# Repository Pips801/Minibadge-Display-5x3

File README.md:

# Minibadge-Display-5x3
 Battery-powered 5x3 SAINTCON Minibadge display

## Description
Battery-powered RP2040 controlled 5x3 minibadge display

MCU: RP2040

Battery: 606090 5000mAh + JST XH 3 pin 2.54mm

BMS: BQ25895

LEDs: WS2812B-2020

## Costs

| Completed?    | Purchase type    | Price   | Cost per item       |
| ------------- | ---------------- | ------- | ------------------- |
| No            | Parts            | $161.01 | $3.22               |
| No            | Main PCB         | $69.00  | $1.38               |
| No            | PCBA             | $101.84 | $2.04               |
| No            | Batteries        | $215.00 | $4.30               |
| No            | Front PCB        | $50.01  | $1.00               |
| No            | PCB Shipping     | $150.00 | $3.00               |
| No            | Battery Shipping | $100.00 | $2.00               |
| **Item quantity** |                  | **Total**   | **Total cost per item** |
| 50            |                  | $846.86 | $16.94              |

| Completed?    | Purchase type    | Price   | Cost per item       |
| ------------- | ---------------- | ------- | ------------------- |
| No            | Parts            | $131.22 | $5.25               |
| No            | Main PCB         | $28.70  | $1.15               |
| No            | PCBA             | $57.11  | $2.28               |
| No            | Batteries        | $107.50 | $4.30               |
| No            | Front PCB        | $37.50  | $1.50               |
| No            | PCB Shipping     | $80.00  | $3.20               |
| No            | Battery Shipping | $53.35  | $2.13               |
| **Item quantity** |                  | **Total**   | **Total cost per item** |
| 25            |                  | $495.38 | $19.82              |

## BOM

|Designator                                                                                        |Footprint                                                 |Quantity|Value            |LCSC Part #|
|--------------------------------------------------------------------------------------------------|----------------------------------------------------------|--------|-----------------|-----------|
|C1, C12, C13, C14, C15, C16, C17, C18, C19                                                        |0603                                                      |9       |4.7μF            |           |
|C10, C11, C20, C21, C22, C23, C24, C25, C26, C27, C28, C29, C34, C35, C36, C37, C38, C39, C40, C41|0402                                                      |20      |0.1μF            |           |
|C2, C3, C6, C7, C9                                                                                |0603                                                      |5       |10μF             |           |
|C31                                                                                               |0402                                                      |1       |1µF              |           |
|C32, C33                                                                                          |0402                                                      |2       |15pF             |           |
|C4                                                                                                |1206                                                      |1       |40μF             |C426659    |
|C5                                                                                                |0402                                                      |1       |47nF             |           |
|C8                                                                                                |0402                                                      |1       |1µF              |C52923     |
|D1                                                                                                |D_SMB                                                     |1       |20v 5A           |C14651     |
|D2, D3, D4, D5, D6, D7, D8, D9                                                                    |LED_WS2812B-2020_PLCC4_2.0x2.0mm                          |8       |WS2812B-2020     |C5349955   |
|J1                                                                                                |PinSocket_2x05_P2.54mm_Vertical_SMD                       |1       |Board to Board   |           |
|J2                                                                                                |JST_XH_S3B-XH-SM4-TB_1x03-1MP_P2.50mm_Horizontal          |1       |BATT JST         |C161860    |
|L1                                                                                                |L_Vishay_IHLP-2525                                        |1       |2.2µH            |C540967    |
|P1                                                                                                |USB_C_Receptacle_HRO_TYPE-C-31-M-12                       |1       |USB_C_Plug_USB2.0|C165948    |
|R1                                                                                                |0603                                                      |1       |5.23kΩ           |           |
|R10, R9                                                                                           |0402                                                      |2       |27.4Ω            |           |
|R11, R12, R13, R14, R15, R16                                                                      |0603                                                      |6       |10kΩ             |           |
|R2                                                                                                |0603                                                      |1       |260Ω             |C861779    |
|R3                                                                                                |0603                                                      |1       |30.1kΩ           |           |
|R4, R5                                                                                            |0603                                                      |2       |5.1k             |           |
|R6, R7, R8                                                                                        |0603                                                      |3       |1kΩ              |           |
|SW1                                                                                               |SW_Push_1P1T_XKB_TS-1187A                                 |1       |USB BOOT         |C318884    |
|U1                                                                                                |Texas_RTW_WQFN-24-1EP_4x4mm_P0.5mm_EP2.7x2.7mm_ThermalVias|1       |BQ25895          |C80200     |
|U10                                                                                               |Crystal_SMD_Abracon_ABM8G-4Pin_3.2x2.5mm                  |1       |ABM8-272-T3      |C20625731  |
|U2                                                                                                |SOIC-8_5.23x5.23mm_P1.27mm                                |1       |W25Q32JVSS       |C82344     |
|U3                                                                                                |QFN-10-RSE                                                |1       |TS3USB221A       |C128396    |
|U4, U5, U6, U7                                                                                    |SOT-223-3_TabPin2                                         |4       |AP7361C-33E      |C500795    |
|U8                                                                                                |SOIC-8_3.9x4.9mm_P1.27mm                                  |1       |TPM8837C         |C7436831   |
|U9                                                                                                |QFN-56-1EP_7x7mm_P0.4mm_EP3.2x3.2mm_ThermalVias           |1       |RP2040           |C2040      |

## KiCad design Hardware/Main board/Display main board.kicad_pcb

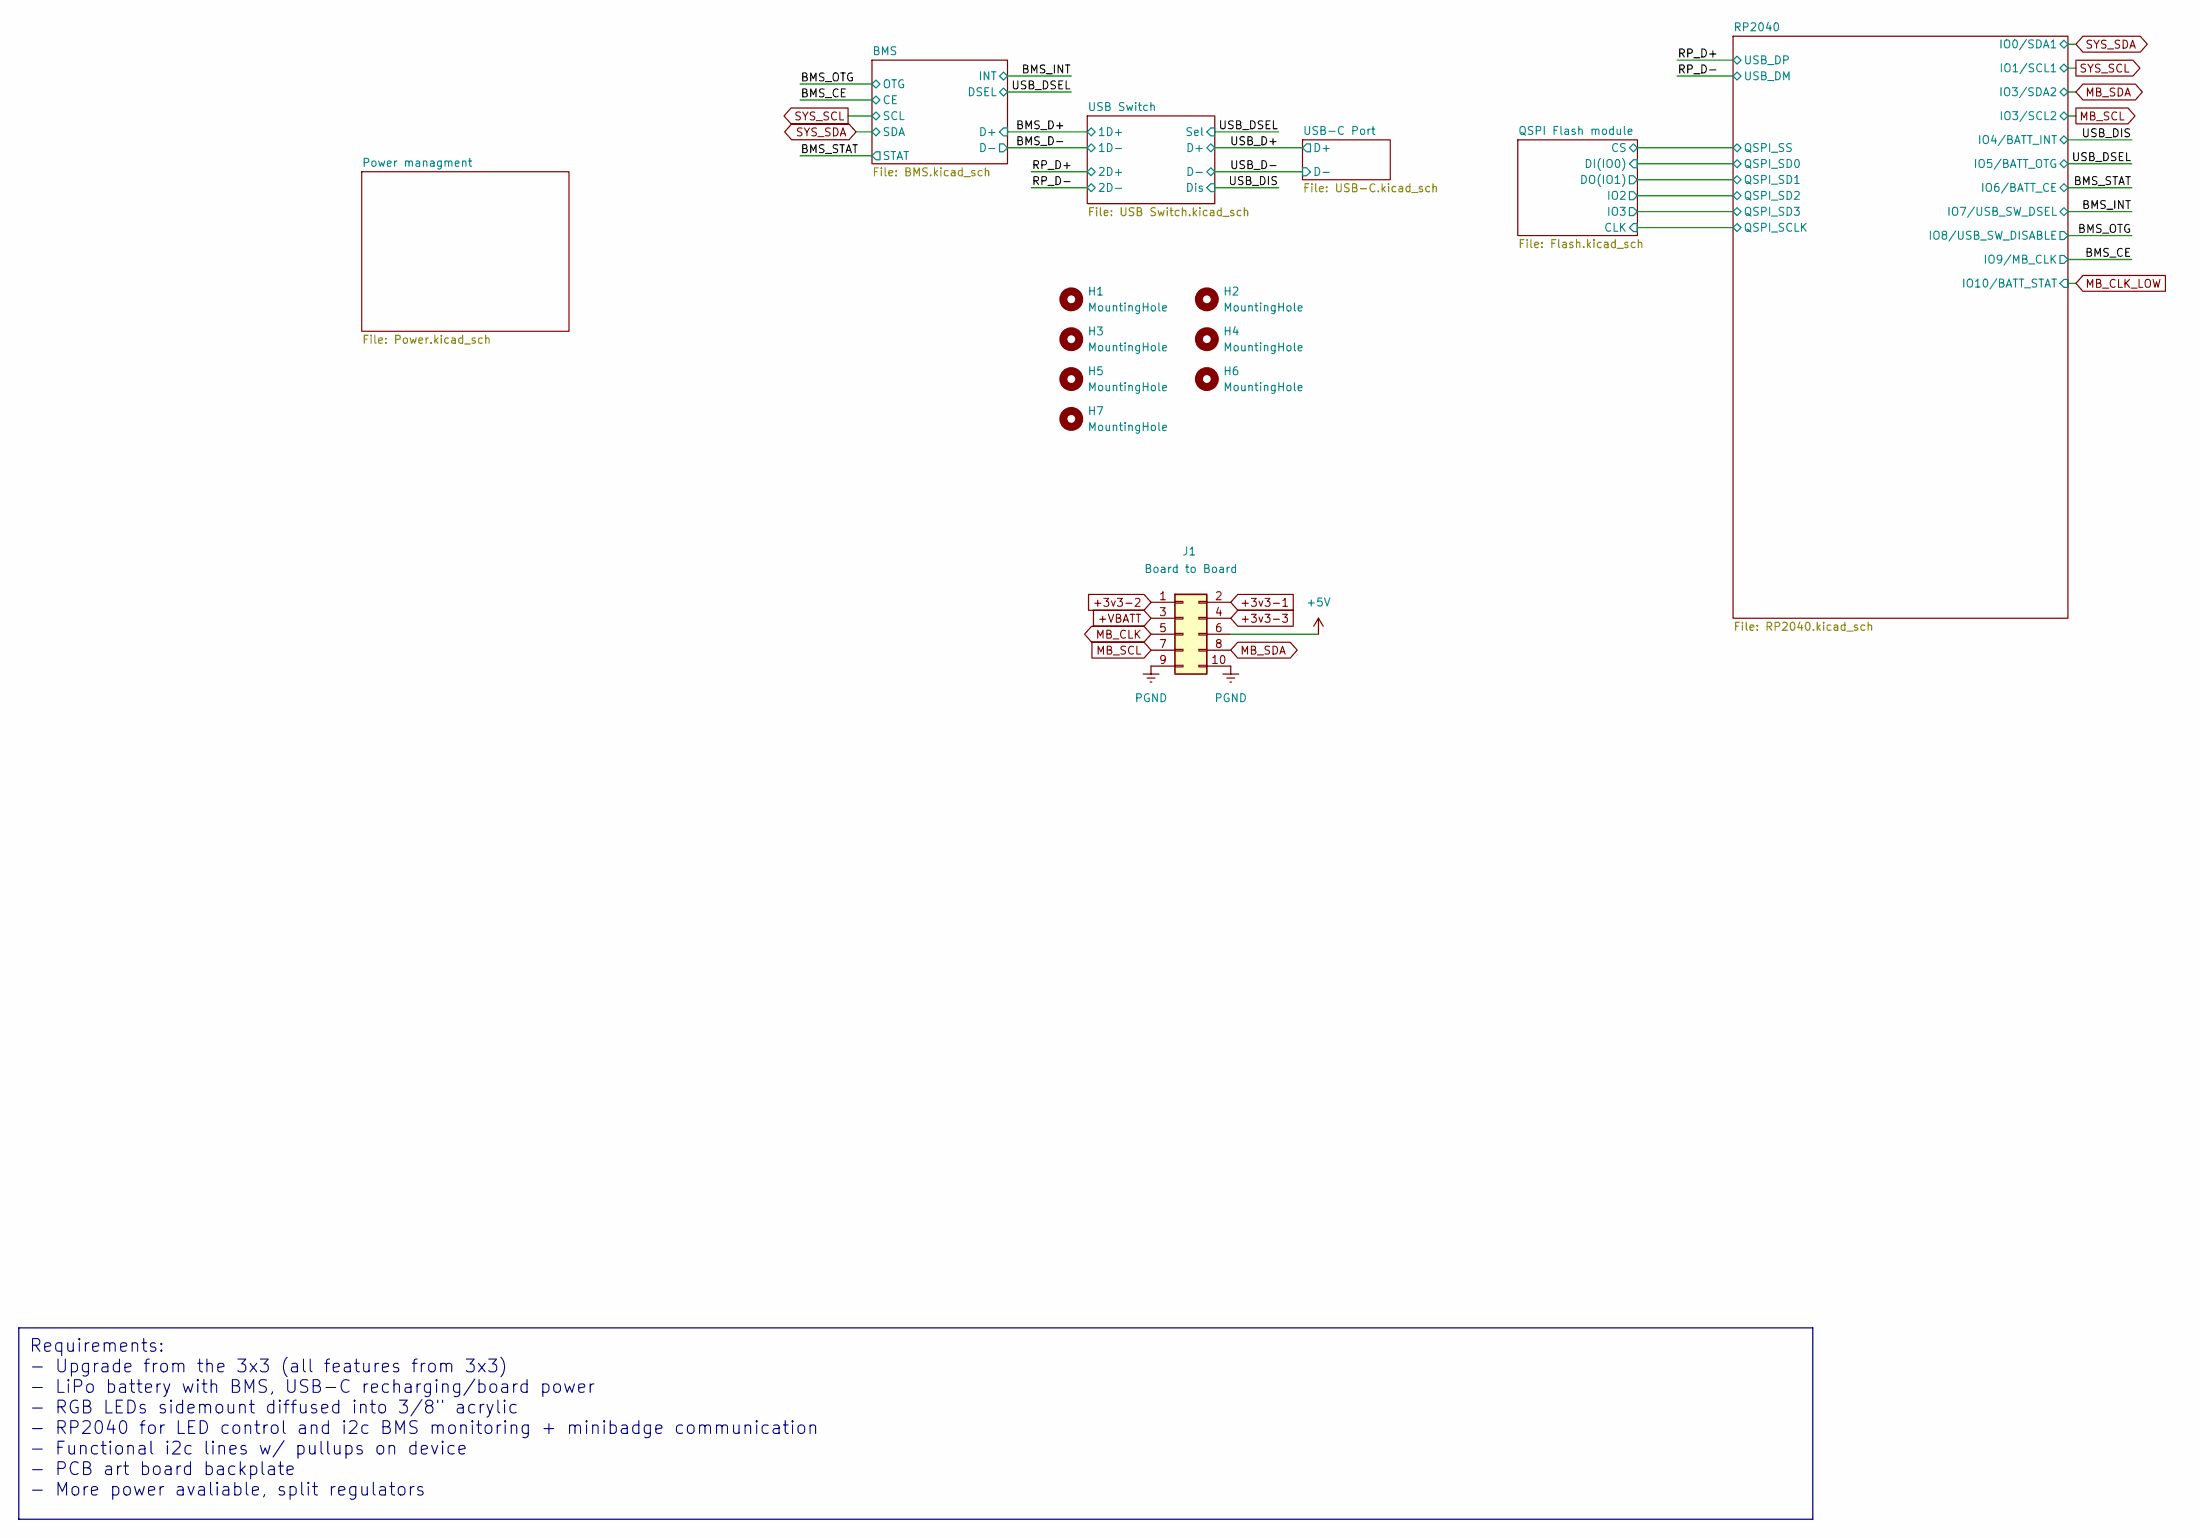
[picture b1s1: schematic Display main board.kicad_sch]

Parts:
H1, H2, H3, H4, H5, H6, H7: MountingHole; MountingHole_2.2mm_M2
J1: Board to Board; PinSocket_2x05_P2.54mm_Vertical_SMD

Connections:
+3v3-1: J1.2; also elsewhere on the board
+3v3-2: J1.1; also elsewhere on the board
+3v3-3: J1.4; also elsewhere on the board
+5V: J1.6; also elsewhere on the board
+VBATT: J1.3; also elsewhere on the board
MB_CLK: J1.5; also elsewhere on the board
MB_SCL: J1.7; also elsewhere on the board
MB_SDA: J1.8; also elsewhere on the board
PGND: J1.9, J1.10; also elsewhere on the board

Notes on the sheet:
Requirements: - Upgrade from the 3x3 (all features from 3x3) - LiPo battery with BMS, USB-C recharging/board power - RGB LEDs sidemount diffused into 3/8" acrylic - RP2040 for LED control and i2c BMS monitoring + minibadge communication - Functional i2c lines w/ pullups on device - PCB art board ba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

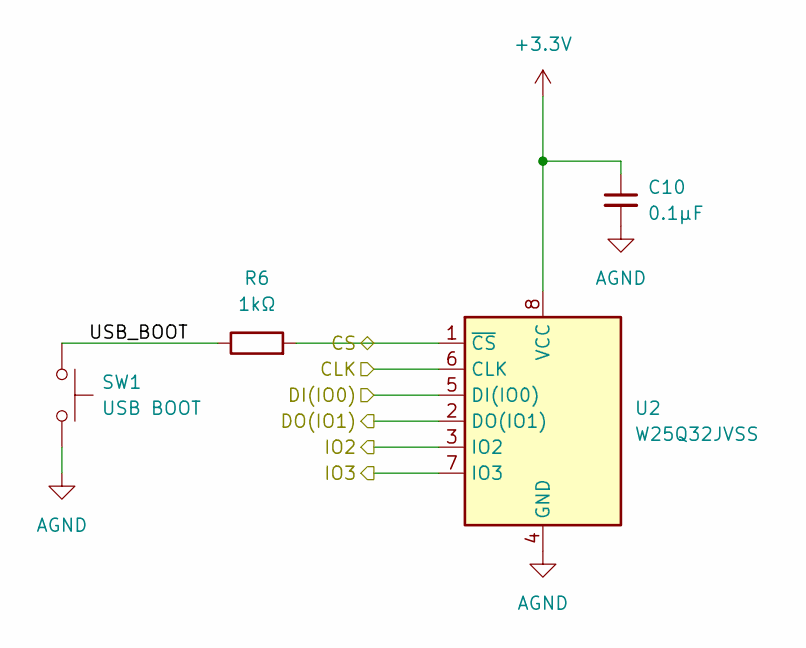
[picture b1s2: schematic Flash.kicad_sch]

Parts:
C10: 0.1μF; C_0402_1005Metric
R6: 1kΩ; R_0603_1608Metric
SW1: USB BOOT; SW_Push_1P1T_XKB_TS-1187A; LCSC Part # C318884
U2: W25Q32JVSS; SOIC-8_5.23x5.23mm_P1.27mm; JLCPCB Part # C82344

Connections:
+3.3V: C10.1, U2.8 (VCC); also elsewhere on the board
/QSPI Flash module/CLK: U2.6 (CLK); also elsewhere on the board
/QSPI Flash module/CS: R6.2, U2.1 (~CS); also elsewhere on the board
/QSPI Flash module/DI(IO0): U2.5 (DI(IO0)); also elsewhere on the board
/QSPI Flash module/DO(IO1): U2.2 (DO(IO1)); also elsewhere on the board
/QSPI Flash module/IO2: U2.3 (IO2); also elsewhere on the board
/QSPI Flash module/IO3: U2.7 (IO3); also elsewhere on the board
/QSPI Flash module/USB_BOOT: R6.1, SW1.1
AGND: C10.2, SW1.2, U2.4 (GND); also elsewhere on the board

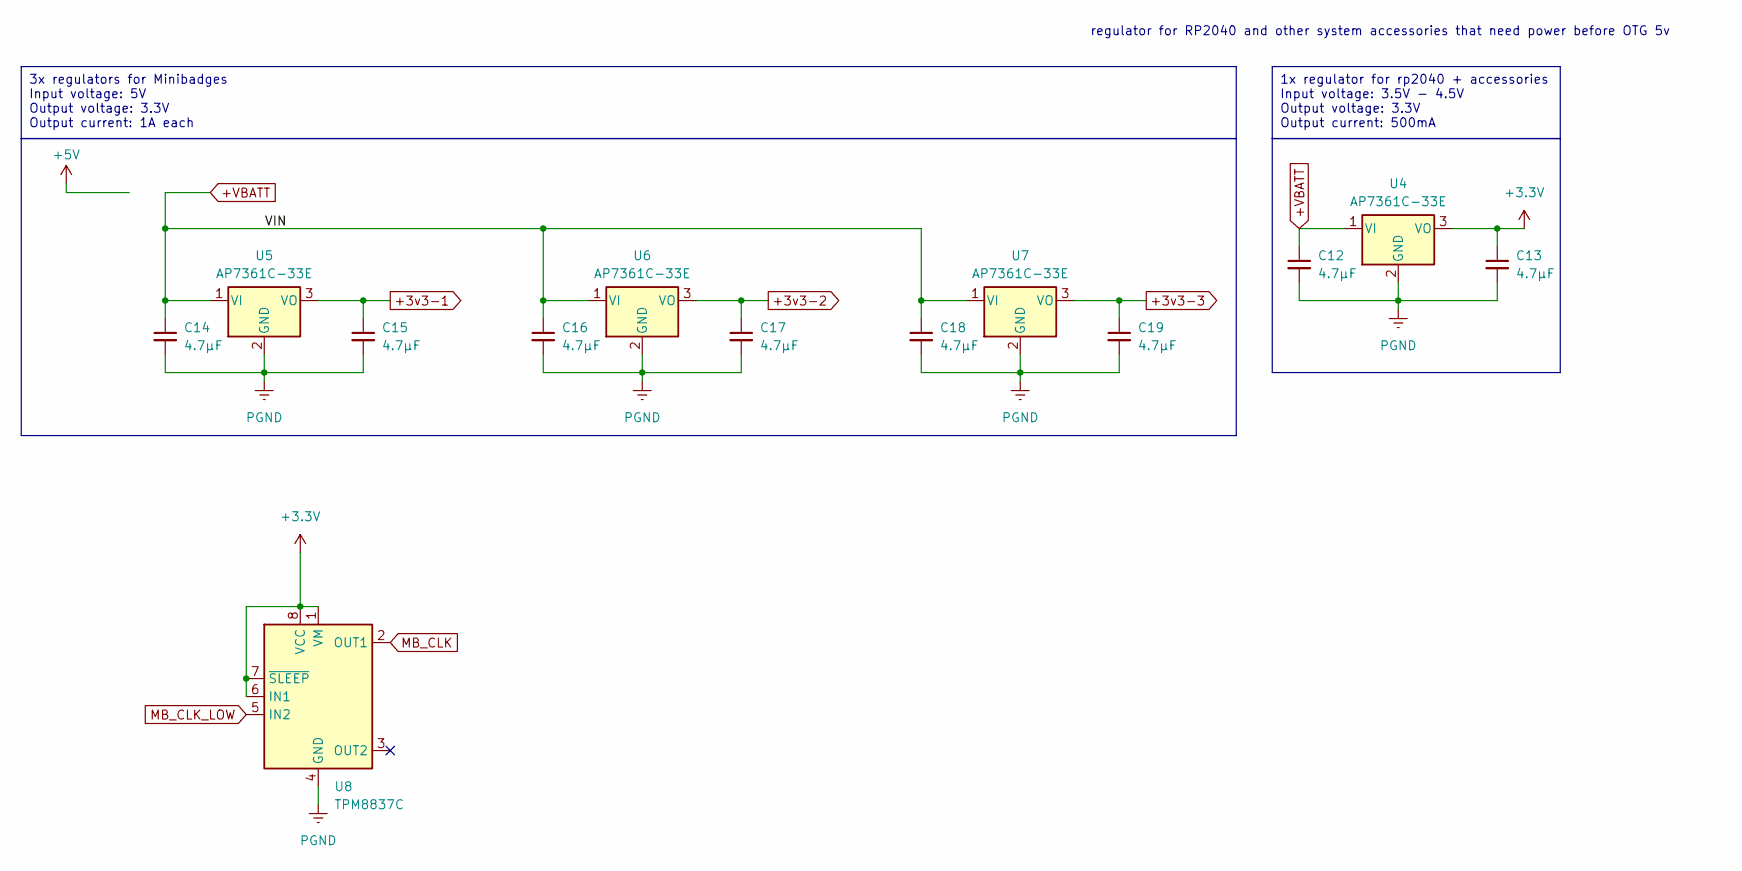
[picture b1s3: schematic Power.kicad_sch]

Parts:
C12, C13, C14, C15, C16, C17, C18, C19: 4.7μF; C_0603_1608Metric
U4, U5, U6, U7: AP7361C-33E; SOT-223-3_TabPin2; JLCPCB Part # C500795
U8: TPM8837C; SOIC-8_3.9x4.9mm_P1.27mm; JLCPCB Part # C7436831

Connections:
+3.3V: C13.1, U4.3 (VO), U8.1 (VM), U8.6 (IN1), U8.7 (~SLEEP), U8.8 (VCC); also elsewhere on the board
+3v3-1: C15.1, U5.3 (VO); also elsewhere on the board
+3v3-2: C17.1, U6.3 (VO); also elsewhere on the board
+3v3-3: C19.1, U7.3 (VO); also elsewhere on the board
+VBATT: C12.1, C14.1, C16.1, C18.1, U4.1 (VI), U5.1 (VI), U6.1 (VI), U7.1 (VI); also elsewhere on the board
MB_CLK: U8.2 (OUT1); also elsewhere on the board
MB_CLK_LOW: U8.5 (IN2); also elsewhere on the board
PGND: C12.2, C13.2, C14.2, C15.2, C16.2, C17.2, C18.2, C19.2, U4.2 (GND), U5.2 (GND), U6.2 (GND), U7.2 (GND), U8.4 (GND), U8.9 (GND); also elsewhere on the board

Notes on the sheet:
1x regulator for rp2040 + accessories Input voltage: 3.5V - 4.5V Output voltage: 3.3V Output current: 500mA
3x regulators for Minibadges Input voltage: 5V Output voltage: 3.3V Output current: 1A each
regulator for RP2040 and other system accessories that need power before OTG 5v

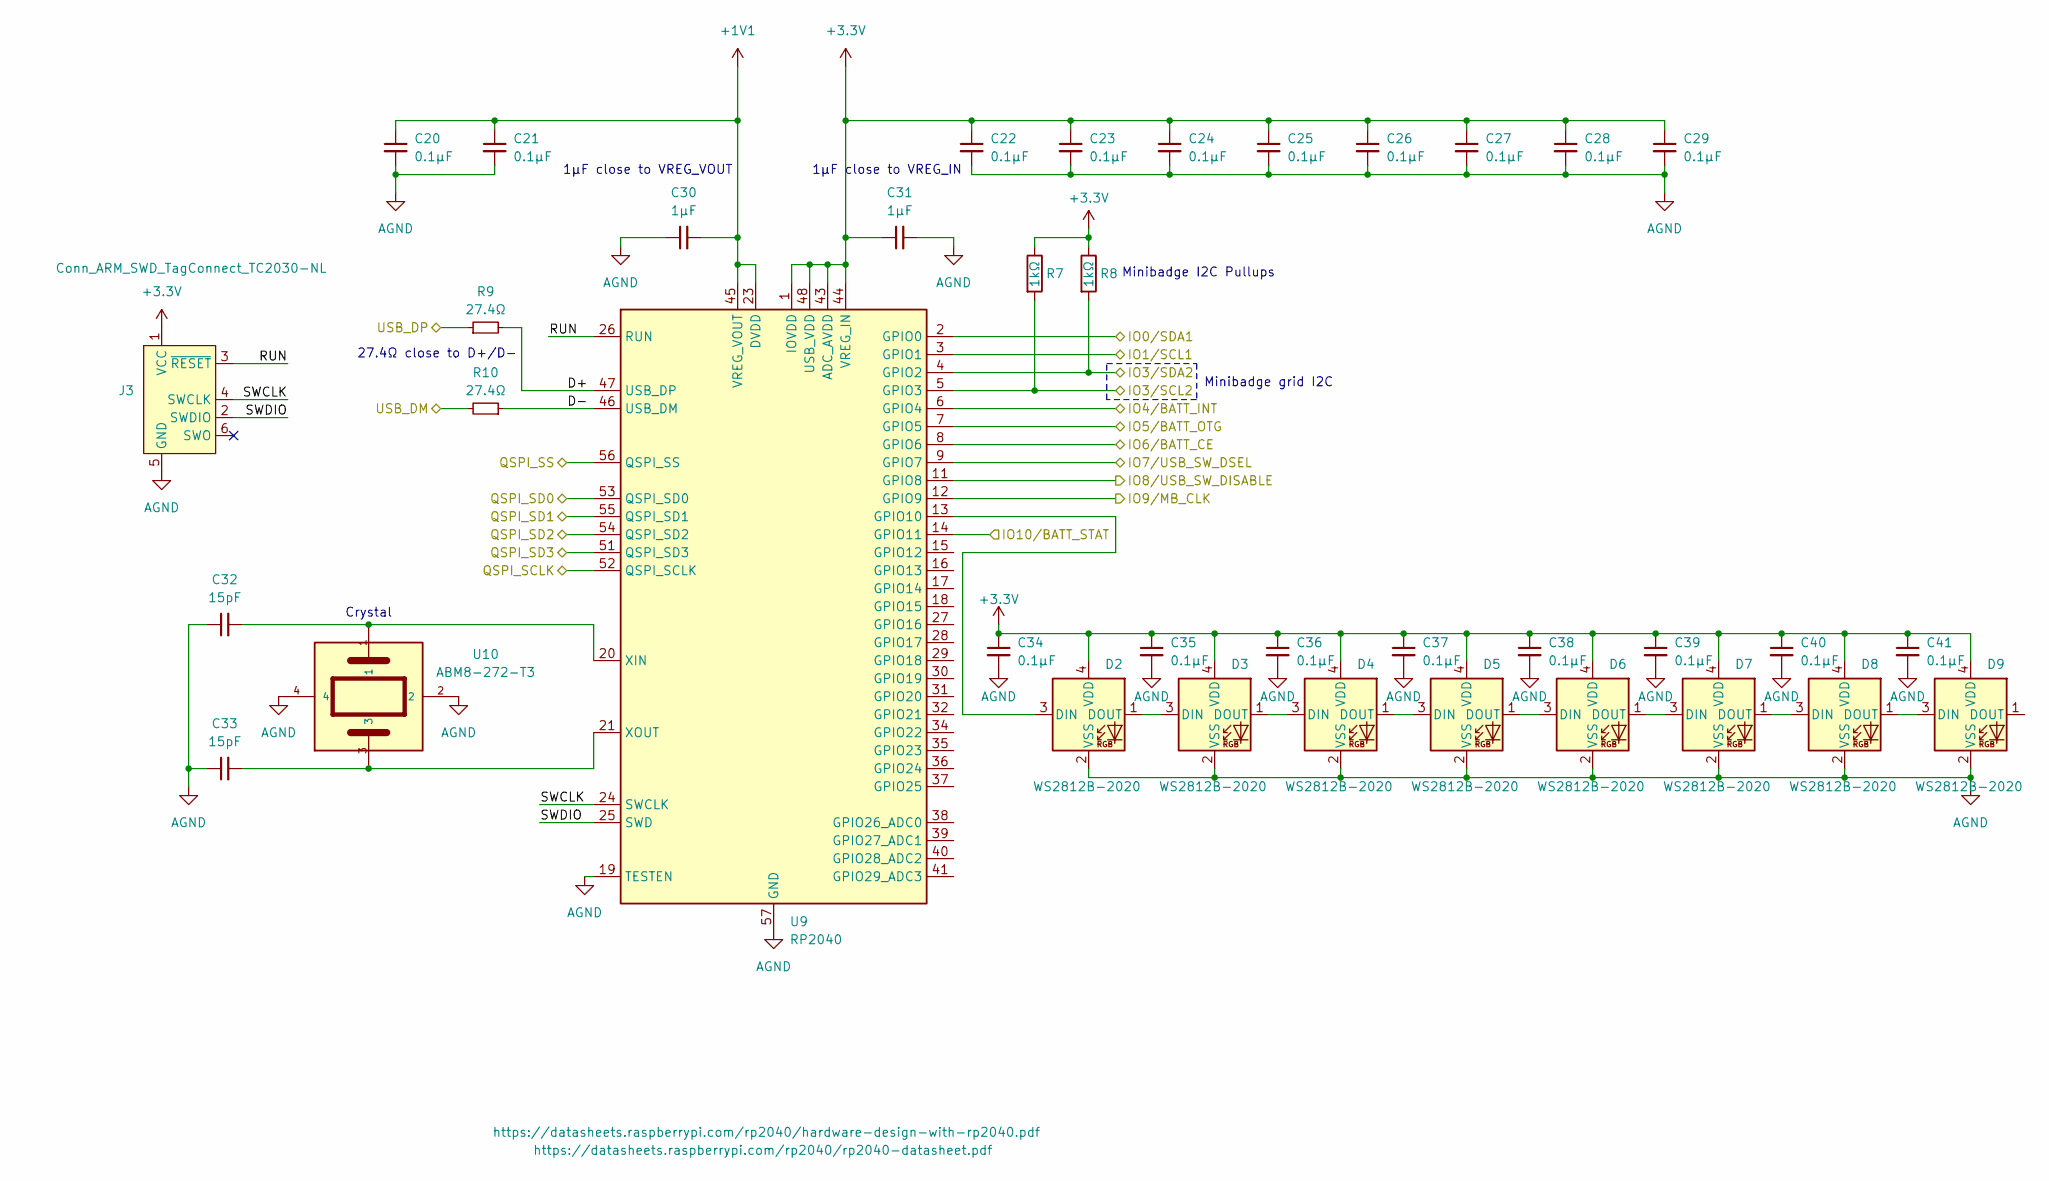
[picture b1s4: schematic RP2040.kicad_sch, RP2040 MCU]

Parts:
C20, C21, C22, C23, C24, C25, C26, C27, C28, C29: 0.1µF; C_0402_1005Metric
C30, C31: 1µF; C_0402_1005Metric
C32, C33: 15pF; C_0402_1005Metric
C34, C35, C36, C37, C38, C39, C40, C41: 0.1μF; C_0402_1005Metric
D2, D3, D4, D5, D6, D7, D8, D9: WS2812B-2020; LED_WS2812B-2020_PLCC4_2.0x2.0mm; JLCPCB Part # C5349955
J3: Conn_ARM_SWD_TagConnect_TC2030-NL; Paw-Connect_RevB_TC2030-IDC-NL_2x03_P1.27mm_Vertical
R7, R8: 1kΩ; R_0603_1608Metric
R9, R10: 27.4Ω; R_0402_1005Metric
U9: RP2040; QFN-56-1EP_7x7mm_P0.4mm_EP3.2x3.2mm_ThermalVias; JLCPCB Part # C2040
U10: ABM8-272-T3; Crystal_SMD_Abracon_ABM8G-4Pin_3.2x2.5mm; JLCPCB Part # C20625731

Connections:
+1V1: C20.1, C21.1, C30.2, U9.23 (DVDD), U9.45 (VREG_VOUT), U9.50 (DVDD)
+3.3V: C22.1, C23.1, C24.1, C25.1, C26.1, C27.1, C28.1, C29.1, C31.1, C34.1, C35.1, C36.1, C37.1, C38.1, C39.1, C40.1, C41.1, D2.4 (VDD), D3.4 (VDD), D4.4 (VDD), D5.4 (VDD), D6.4 (VDD), D7.4 (VDD), D8.4 (VDD), D9.4 (VDD), J3.1 (VCC), R7.1, R8.1, U9.1 (IOVDD), U9.10 (IOVDD), U9.22 (IOVDD), U9.33 (IOVDD), U9.42 (IOVDD), U9.43 (ADC_AVDD), U9.44 (VREG_IN), U9.48 (USB_VDD), U9.49 (IOVDD); also elsewhere on the board
/BMS_CE: U9.12 (GPIO9); also elsewhere on the board
/BMS_INT: U9.9 (GPIO7); also elsewhere on the board
/BMS_OTG: U9.11 (GPIO8); also elsewhere on the board
/BMS_STAT: U9.8 (GPIO6); also elsewhere on the board
/QSPI Flash module/CLK: U9.52 (QSPI_SCLK); also elsewhere on the board
/QSPI Flash module/CS: U9.56 (QSPI_SS); also elsewhere on the board
/QSPI Flash module/DI(IO0): U9.53 (QSPI_SD0); also elsewhere on the board
/QSPI Flash module/DO(IO1): U9.55 (QSPI_SD1); also elsewhere on the board
/QSPI Flash module/IO2: U9.54 (QSPI_SD2); also elsewhere on the board
/QSPI Flash module/IO3: U9.51 (QSPI_SD3); also elsewhere on the board
/RP2040/D+: R9.2, U9.47 (USB_DP)
/RP2040/D-: R10.1, U9.46 (USB_DM)
/RP2040/RUN: J3.3 (~RESET), U9.26 (RUN)
/RP2040/SWCLK: J3.4 (SWCLK), U9.24 (SWCLK)
/RP2040/SWDIO: J3.2 (SWDIO), U9.25 (SWD)
/RP_D+: R9.1; also elsewhere on the board
/RP_D-: R10.2; also elsewhere on the board
/USB_DIS: U9.6 (GPIO4); also elsewhere on the board
/USB_DSEL: U9.7 (GPIO5); also elsewhere on the board
AGND: C20.2, C21.2, C22.2, C23.2, C24.2, C25.2, C26.2, C27.2, C28.2, C29.2, C30.1, C31.2, C32.1, C33.1, C34.2, C35.2, C36.2, C37.2, C38.2, C39.2, C40.2, C41.2, D2.2 (VSS), D3.2 (VSS), D4.2 (VSS), D5.2 (VSS), D6.2 (VSS), D7.2 (VSS), D8.2 (VSS), D9.2 (VSS), J3.5 (GND), U9.19 (TESTEN), U9.57 (GND), U10.2, U10.4; also elsewhere on the board
MB_CLK_LOW: U9.14 (GPIO11); also elsewhere on the board
MB_SCL: R7.2, U9.5 (GPIO3); also elsewhere on the board
MB_SDA: R8.2, U9.4 (GPIO2); also elsewhere on the board
unnamed: D2.3 (DIN), U9.13 (GPIO10)
unnamed: D2.1 (DOUT), D3.3 (DIN)
unnamed: D3.1 (DOUT), D4.3 (DIN)
unnamed: D4.1 (DOUT), D5.3 (DIN)
unnamed: D5.1 (DOUT), D6.3 (DIN)
unnamed: D6.1 (DOUT), D7.3 (DIN)
unnamed: D7.1 (DOUT), D8.3 (DIN)
unnamed: D8.1 (DOUT), D9.3 (DIN)
unnamed: C32.2, U9.20 (XIN), U10.1
unnamed: C33.2, U9.21 (XOUT), U10.3
SYS_SCL: U9.3 (GPIO1); also elsewhere on the board
SYS_SDA: U9.2 (GPIO0); also elsewhere on the board

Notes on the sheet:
1µF close to VREG_VOUT
27.4Ω close to D+/D-
Minibadge grid I2C
Crystal
Minibadge I2C Pullups
1µF close to VREG_IN

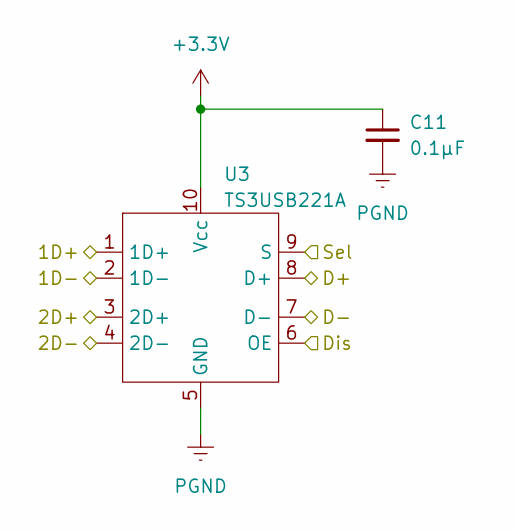
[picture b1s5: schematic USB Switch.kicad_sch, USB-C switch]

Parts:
C11: 0.1μF; C_0402_1005Metric
U3: TS3USB221A; QFN-10-RSE; JLCPCB Part # C128396

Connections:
+3.3V: C11.1, U3.10 (Vcc); also elsewhere on the board
/BMS_D+: U3.1 (1D+); also elsewhere on the board
/BMS_D-: U3.2 (1D-); also elsewhere on the board
/RP_D+: U3.3 (2D+); also elsewhere on the board
/RP_D-: U3.4 (2D-); also elsewhere on the board
/USB_D+: U3.8 (D+); also elsewhere on the board
/USB_D-: U3.7 (D-); also elsewhere on the board
/USB_DIS: U3.6 (OE); also elsewhere on the board
/USB_DSEL: U3.9 (S); also elsewhere on the board
PGND: C11.2, U3.5 (GND); also elsewhere on the board

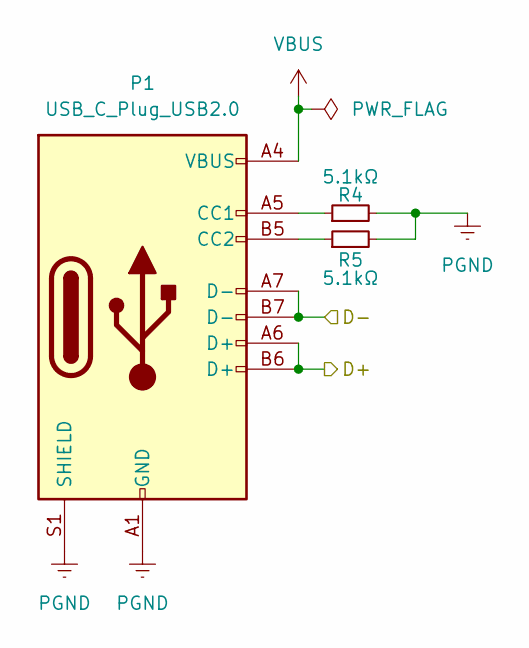
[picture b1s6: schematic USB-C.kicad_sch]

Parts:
P1: USB_C_Plug_USB2.0; USB_C_Receptacle_HRO_TYPE-C-31-M-12; JLCPCB Part # C165948
R4, R5: 5.1kΩ; R_0603_1608Metric

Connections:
/USB_D+: P1.A6 (D+), P1.B6 (D+); also elsewhere on the board
/USB_D-: P1.A7 (D-), P1.B7 (D-); also elsewhere on the board
unnamed: P1.A5 (CC1), R4.1
unnamed: P1.B5 (CC2), R5.1
PGND: P1.A1 (GND), P1.A12 (GND), P1.B1 (GND), P1.B12 (GND), P1.S1 (SHIELD), R4.2, R5.2; also elsewhere on the board
VBUS: P1.A4 (VBUS), P1.A9 (VBUS), P1.B4 (VBUS), P1.B9 (VBUS); also elsewhere on the board

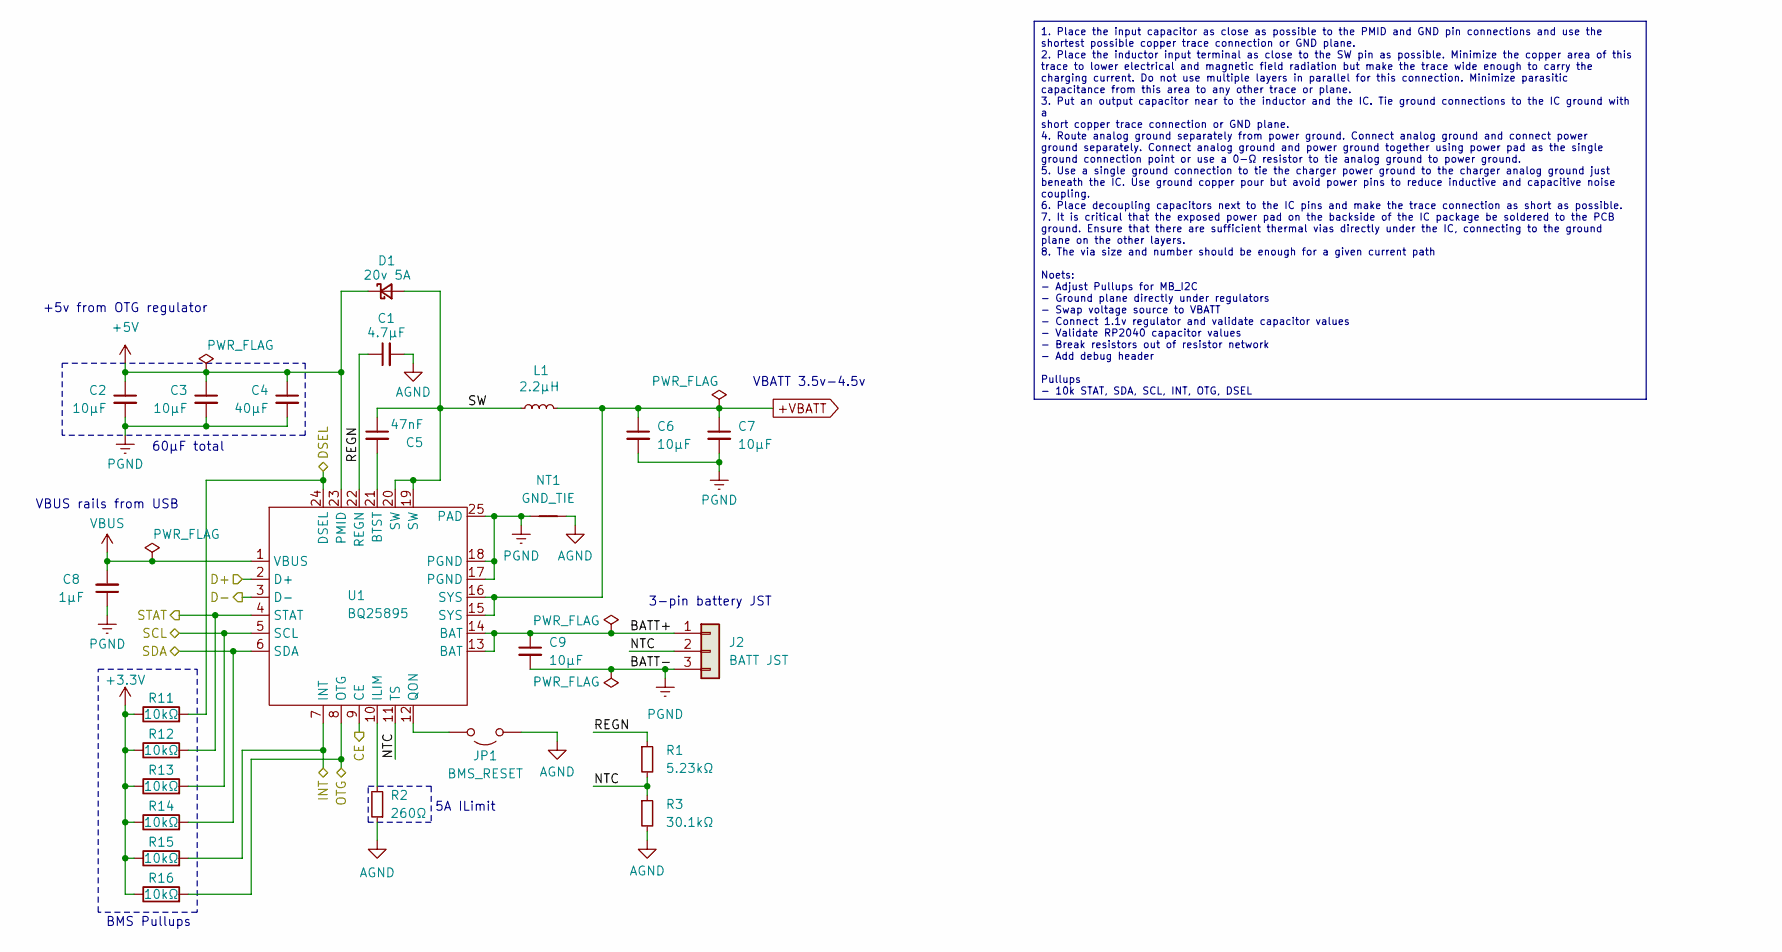
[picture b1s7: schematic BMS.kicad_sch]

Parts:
C1: 4.7μF; C_0603_1608Metric
C2, C3: 10μF; C_0603_1608Metric
C4: 40μF; C_1206_3216Metric; LCSC Part # C426659
C5: 47nF; C_0402_1005Metric
C6, C7, C9: 10µF; C_0603_1608Metric
C8: 1µF; C_0402_1005Metric; LCSC Part # C52923
D1: 20v 5A; D_SMB; LCSC Part # C14651
J2: BATT JST; JST_XH_S3B-XH-SM4-TB_1x03-1MP_P2.50mm_Horizontal; JLCPCB Part # C161860
JP1: BMS_RESET; SolderJumper-2_P1.3mm_Open_RoundedPad1.0x1.5mm
L1: 2.2µH; L_Vishay_IHLP-2525; LCSC Part # C540967
NT1: GND_TIE; NetTie-2_SMD_Pad0.5mm
R1: 5.23kΩ; R_0603_1608Metric
R2: 260Ω; R_0603_1608Metric; LCSC Part # C861779
R3: 30.1kΩ; R_0603_1608Metric
R11, R12, R13, R14, R15, R16: 10kΩ; R_0603_1608Metric
U1: BQ25895; Texas_RTW_WQFN-24-1EP_4x4mm_P0.5mm_EP2.7x2.7mm_ThermalVias; LCSC Part # C80200

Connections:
+3.3V: R11.1, R12.1, R13.1, R14.1, R15.1, R16.1; also elsewhere on the board
+5V: C2.1, C3.1, C4.1, D1.1 (K), U1.23 (PMID); also elsewhere on the board
+VBATT: C6.1, C7.1, L1.1, U1.15 (SYS), U1.16 (SYS); also elsewhere on the board
/BMS/BATT+: C9.1, J2.1, U1.13 (BAT), U1.14 (BAT)
/BMS/NTC: J2.2, R1.2, R3.1, U1.11 (TS)
/BMS/REGN: C1.1, R1.1, U1.22 (REGN)
/BMS/SW: C5.1, D1.2 (A), L1.2, U1.19 (SW), U1.20 (SW)
/BMS_CE: U1.9 (CE); also elsewhere on the board
/BMS_D+: U1.2 (D+); also elsewhere on the board
/BMS_D-: U1.3 (D-); also elsewhere on the board
/BMS_INT: R15.2, U1.7 (INT); also elsewhere on the board
/BMS_OTG: R16.2, U1.8 (OTG); also elsewhere on the board
/BMS_STAT: R12.2, U1.4 (STAT); also elsewhere on the board
/USB_DSEL: R11.2, U1.24 (DSEL); also elsewhere on the board
AGND: C1.2, JP1.1 (A), NT1.1, R2.1, R3.2; also elsewhere on the board
unnamed: JP1.2 (B), U1.12 (QON)
unnamed: C5.2, U1.21 (BTST)
unnamed: R2.2, U1.10 (ILIM)
PGND: C2.2, C3.2, C4.2, C6.2, C7.2, C8.1, C9.2, J2.3, NT1.2, U1.17 (PGND), U1.18 (PGND), U1.25 (PAD); also elsewhere on the board
SYS_SCL: R13.2, U1.5 (SCL); also elsewhere on the board
SYS_SDA: R14.2, U1.6 (SDA); also elsewhere on the board
VBUS: C8.2, U1.1 (VBUS); also elsewhere on the board

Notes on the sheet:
1. Place the input capacitor as close as possible to the PMID and GND pin connections and use the shortest possible copper trace connection or GND plane. 2. Place the inductor input terminal as close to the SW pin as possible. Minimize the copper area of this trace to lower electrical and magnetic 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
BMS Pullups
3-pin battery JST
VBUS rails from USB
5A ILimit
60μF total
+5v from OTG regulator
VBATT 3.5v-4.5v

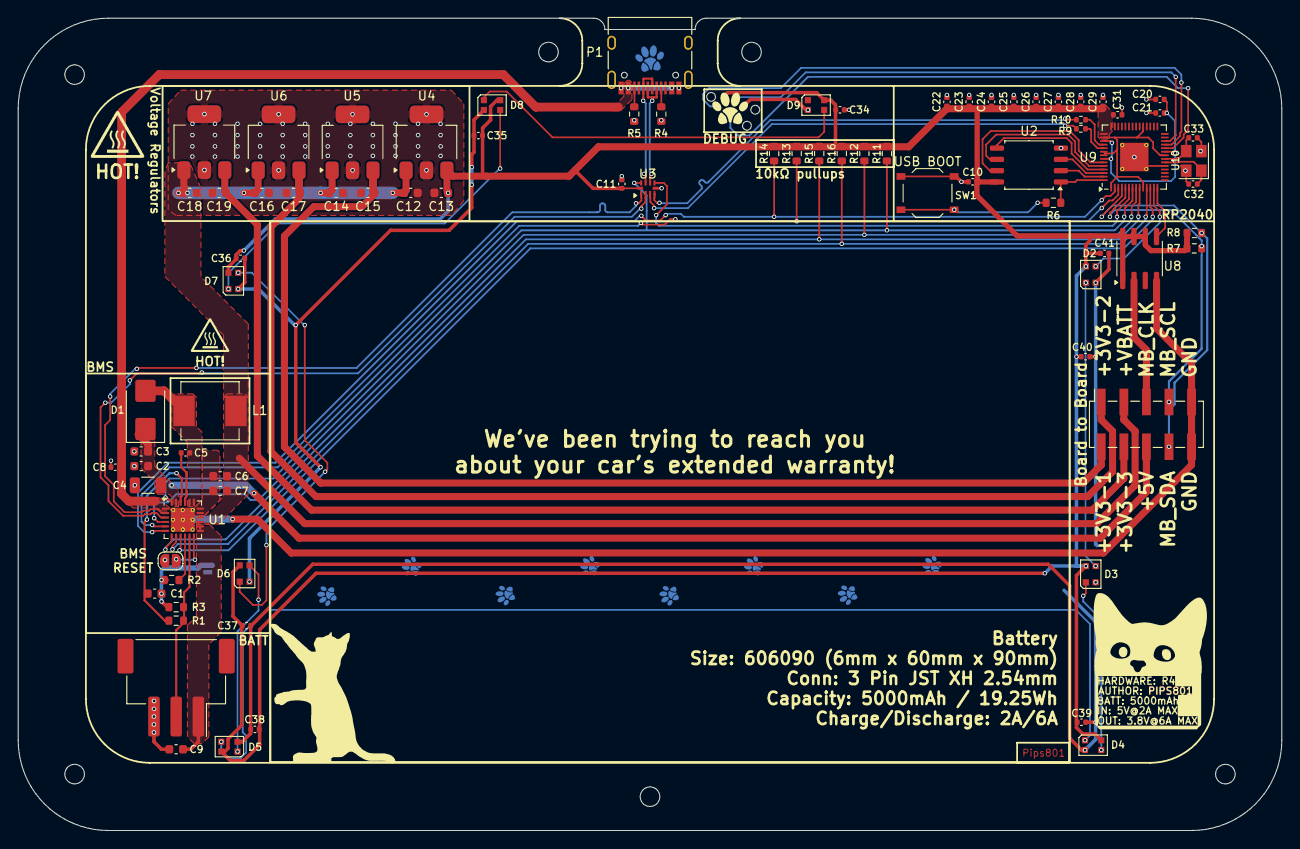
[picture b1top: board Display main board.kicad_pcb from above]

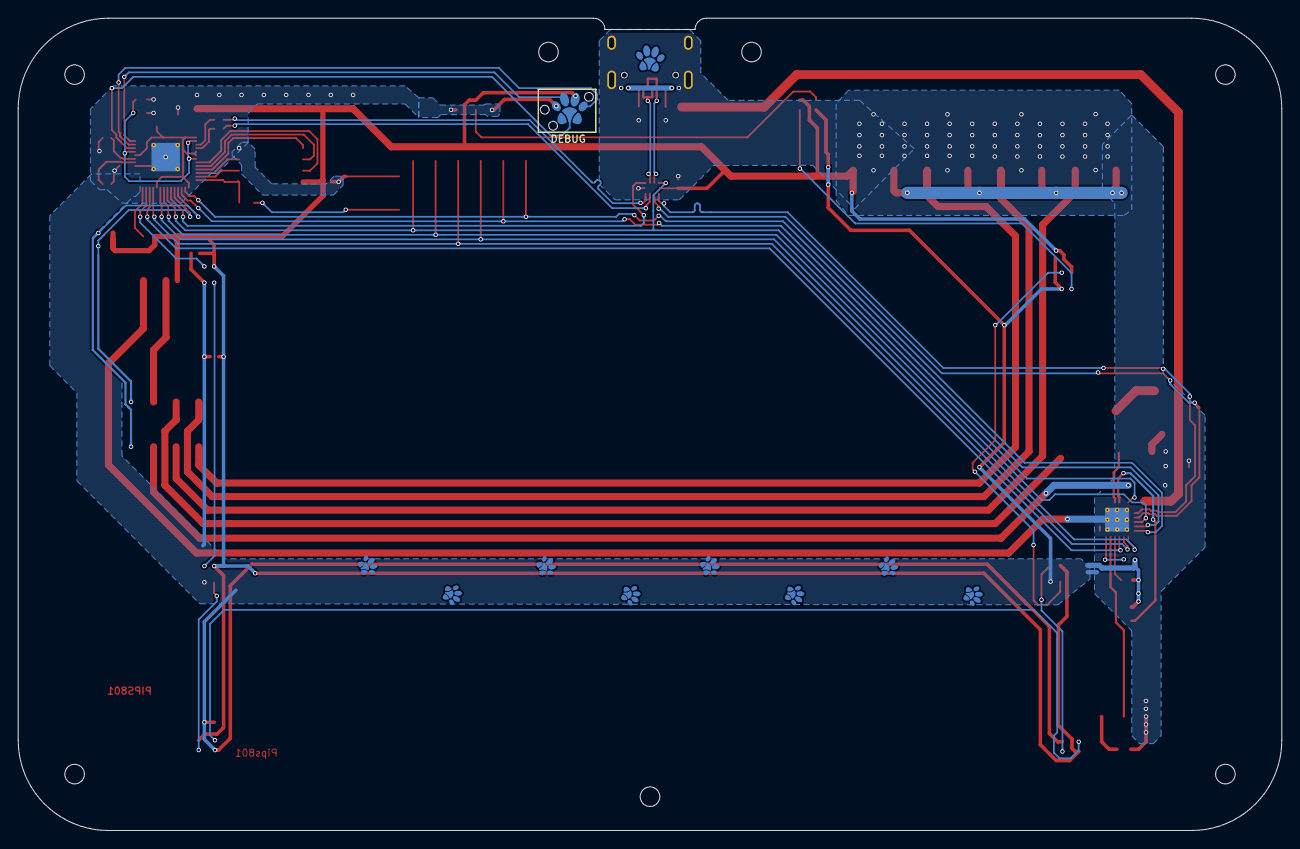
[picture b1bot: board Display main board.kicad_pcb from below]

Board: 2 copper layers, 142.2 x 91.4 mm, 100 parts (11 on the bottom side), 59 nets.

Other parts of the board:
G**: Paw-Connect_Silk_RevB
G**#2, G**#3, G**#4, G**#5, G**#6, G**#7, G**#8, G**#9, G**#10: Paw-Connect_Silk_RevB

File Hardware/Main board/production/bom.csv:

Designator,Footprint,Quantity,Value,LCSC Part #
"C1, C12, C13, C14, C15, C16, C17, C18, C19",0603,9,4.7μF,
"C10, C11, C20, C21, C22, C23, C24, C25, C26, C27, C28, C29, C34, C35, C36, C37, C38, C39, C40, C41",0402,20,0.1μF,
"C2, C3, C6, C7, C9",0603,5,10μF,
C31,0402,1,1µF,
"C32, C33",0402,2,15pF,
C4,1206,1,40μF,C426659
C5,0402,1,47nF,
C8,0402,1,1µF,C52923
D1,D_SMB,1,20v 5A,C14651
"D2, D3, D4, D5, D6, D7, D8, D9",LED_WS2812B-2020_PLCC4_2.0x2.0mm,8,WS2812B-2020,C5349955
J1,PinSocket_2x05_P2.54mm_Vertical_SMD,1,Board to Board,
J2,JST_XH_S3B-XH-SM4-TB_1x03-1MP_P2.50mm_Horizontal,1,BATT JST,C161860
L1,L_Vishay_IHLP-2525,1,2.2µH,C540967
P1,USB_C_Receptacle_HRO_TYPE-C-31-M-12,1,USB_C_Plug_USB2.0,C165948
R1,0603,1,5.23kΩ,
"R10, R9",0402,2,27.4Ω,
"R11, R12, R13, R14, R15, R16",0603,6,10kΩ,
R2,0603,1,260Ω,C861779
R3,0603,1,30.1kΩ,
"R4, R5",0603,2,5.1k,
"R6, R7, R8",0603,3,1kΩ,
SW1,SW_Push_1P1T_XKB_TS-1187A,1,USB BOOT,C318884
U1,Texas_RTW_WQFN-24-1EP_4x4mm_P0.5mm_EP2.7x2.7mm_ThermalVias,1,BQ25895,C80200
U10,Crystal_SMD_Abracon_ABM8G-4Pin_3.2x2.5mm,1,ABM8-272-T3,C20625731
U2,SOIC-8_5.23x5.23mm_P1.27mm,1,W25Q32JVSS,C82344
U3,QFN-10-RSE,1,TS3USB221A,C128396
"U4, U5, U6, U7",SOT-223-3_TabPin2,4,AP7361C-33E,C500795
U8,SOIC-8_3.9x4.9mm_P1.27mm,1,TPM8837C,C7436831
U9,QFN-56-1EP_7x7mm_P0.4mm_EP3.2x3.2mm_ThermalVias,1,RP2040,C2040
